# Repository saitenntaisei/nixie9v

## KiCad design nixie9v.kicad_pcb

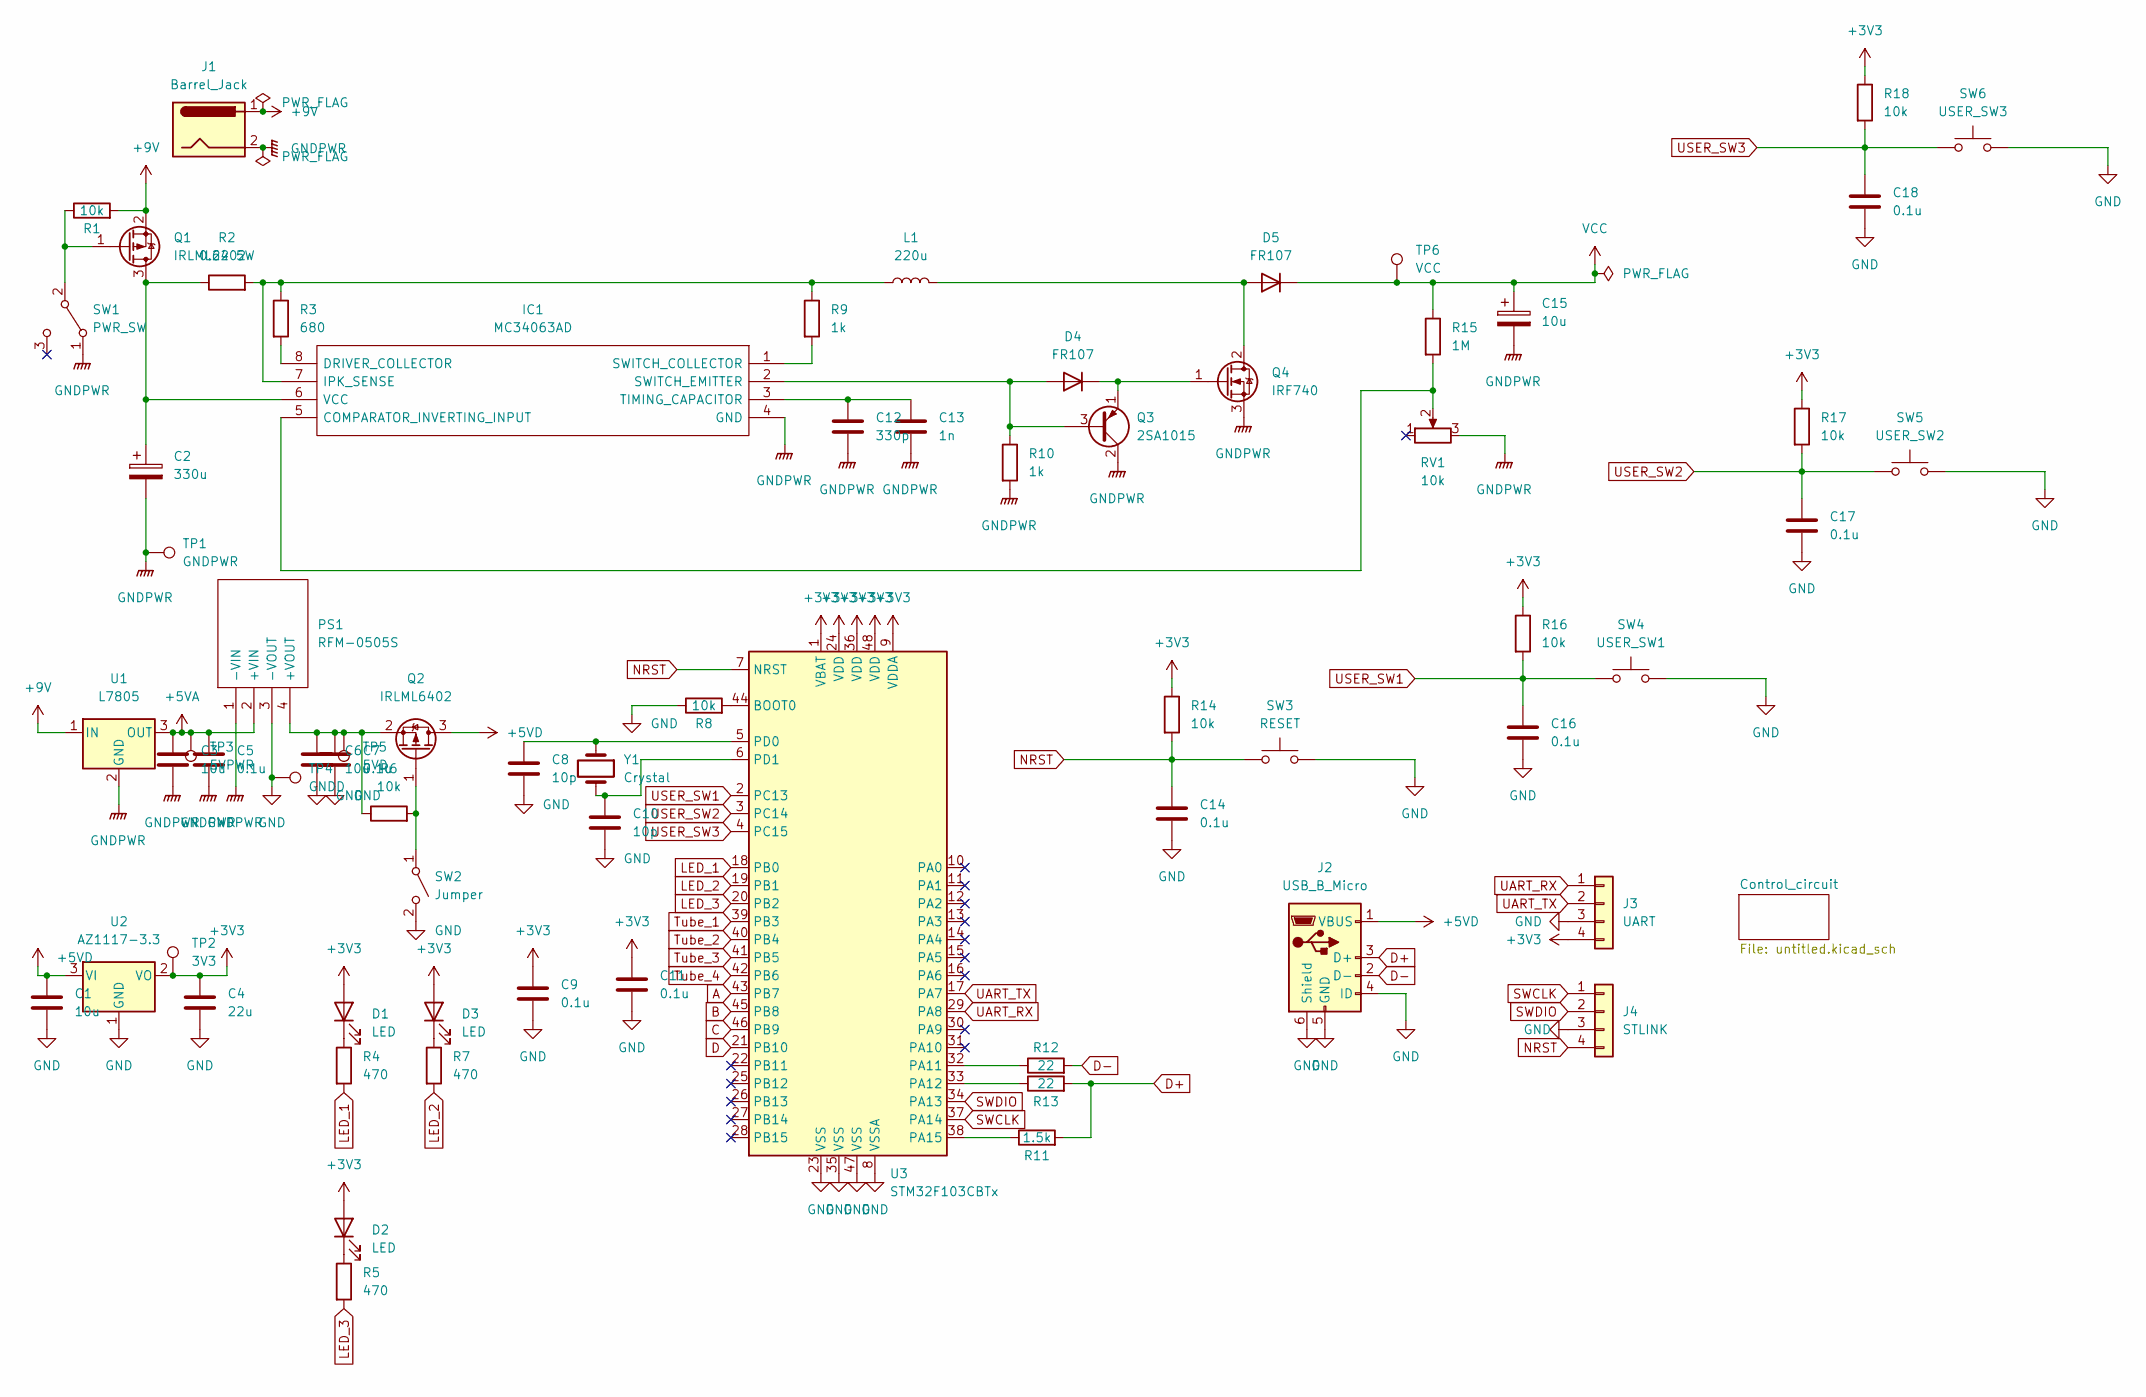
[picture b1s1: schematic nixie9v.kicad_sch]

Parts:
C1, C3, C6: 10u; C_0603_1608Metric_Pad1.08x0.95mm_HandSolder
C2: 330u; CP_Radial_D10.0mm_P3.50mm
C4: 22u; C_0603_1608Metric_Pad1.08x0.95mm_HandSolder
C5, C7, C9, C11, C14, C16, C17, C18: 0.1u; C_0603_1608Metric_Pad1.08x0.95mm_HandSolder
C8, C10: 10p; C_0603_1608Metric_Pad1.08x0.95mm_HandSolder
C12: 330p; C_0603_1608Metric_Pad1.08x0.95mm_HandSolder
C13: 1n; C_0603_1608Metric_Pad1.08x0.95mm_HandSolder
C15: 10u; CP_Radial_D10.0mm_P3.50mm
D1, D2, D3: LED; LED_0603_1608Metric_Pad1.05x0.95mm_HandSolder
D4, D5: FR107; D_DO-41_SOD81_P7.62mm_Horizontal
IC1: MC34063AD; SOIC127P600X175-8N; Manufacturer_Part_Number MC34063AD; Mouser Part Number 512-MC34063AD
J1: Barrel_Jack; BarrelJack_Horizontal
J2: USB_B_Micro; USB_Micro-B_Wuerth_629105150521_CircularHoles
J3: UART; JST_SH_BM04B-SRSS-TB_1x04-1MP_P1.00mm_Vertical
J4: STLINK; JST_SH_BM04B-SRSS-TB_1x04-1MP_P1.00mm_Vertical
L1: 220u; L_Toroid_Horizontal_D24.1mm_P21.80mm_Bourns_2200
PS1: RFM-0505S; RFM0505S; Manufacturer_Part_Number RFM-0505S; Mouser Part Number 919-RFM-0505S
Q1, Q2: IRLML6402; SOT-23
Q3: 2SA1015; TO-92
Q4: IRF740; TO-220-3_Vertical
R1, R6, R8, R14, R16, R17, R18: 10k; R_0603_1608Metric_Pad0.98x0.95mm_HandSolder
R2: 0.22 5W; RESM17073X710N
R3: 680; R_0603_1608Metric_Pad0.98x0.95mm_HandSolder
R4, R5, R7: 470; R_0603_1608Metric_Pad0.98x0.95mm_HandSolder
R9, R10: 1k; R_0603_1608Metric_Pad0.98x0.95mm_HandSolder
R11: 1.5k; R_0603_1608Metric_Pad0.98x0.95mm_HandSolder
R12, R13: 22; R_0603_1608Metric_Pad0.98x0.95mm_HandSolder
R15: 1M; R_0603_1608Metric_Pad0.98x0.95mm_HandSolder
RV1: 10k; 3362P_1
SW1: PWR_SW; PinHeader_1x03_P2.54mm_Vertical
SW2: Jumper; PinHeader_1x02_P2.54mm_Vertical
SW3: RESET; SW_SPST_EVQP2
SW4: USER_SW1; SW_SPST_EVQP2
SW5: USER_SW2; SW_SPST_EVQP2
SW6: USER_SW3; SW_SPST_EVQP2
TP1: GNDPWR; TestPoint_THTPad_D2.5mm_Drill1.2mm
TP2: 3V3; TestPoint_THTPad_D2.5mm_Drill1.2mm
TP3: 5VPWR; TestPoint_THTPad_D2.5mm_Drill1.2mm
TP4: GNDD; TestPoint_THTPad_D2.5mm_Drill1.2mm
TP5: 5VD; TestPoint_THTPad_D2.5mm_Drill1.2mm
TP6: VCC; TestPoint_THTPad_D2.5mm_Drill1.2mm
U1: L7805; TO-220-3_Vertical
U2: AZ1117-3.3; SOT-223-3_TabPin2
U3: STM32F103CBTx; LQFP-48_7x7mm_P0.5mm
Y1: Crystal; Crystal_SMD_SeikoEpson_MA505-2Pin_12.7x5.1mm_HandSoldering

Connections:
+3V3: C4.1, C9.1, C11.1, D1.2 (A), D2.2 (A), D3.2 (A), J3.4, R14.1, R16.1, R17.1, R18.1, TP2.1, U2.2 (VO), U3.1 (VBAT), U3.9 (VDDA), U3.24 (VDD), U3.36 (VDD), U3.48 (VDD); also elsewhere on the board
+5VA: C3.1, C5.1, PS1.2 (+VIN), TP3.1, U1.3 (OUT); also elsewhere on the board
+5VD: C1.1, J2.1 (VBUS), Q2.3 (D), U2.3 (VI)
+9V: J1.1, Q1.2 (S), R1.2, U1.1 (IN)
A: U3.43 (PB7); also elsewhere on the board
B: U3.45 (PB8); also elsewhere on the board
C: U3.46 (PB9); also elsewhere on the board
D: U3.21 (PB10); also elsewhere on the board
D+: J2.3 (D+), R11.2, R13.2
D-: J2.2 (D-), R12.2
GND: C1.2, C4.2, C6.2, C7.2, C8.2, C9.2, C10.2, C11.2, C14.2, C16.2, C17.2, C18.2, J2.4 (ID), J2.5 (GND), J2.6 (Shield), J3.3, J4.3, PS1.3 (-VOUT), R8.1, SW2.2 (B), SW3.2, SW4.2, SW5.2, SW6.2, TP4.1, U2.1 (GND), U3.8 (VSSA), U3.23 (VSS), U3.35 (VSS), U3.47 (VSS); also elsewhere on the board
LED_1: R4.2, U3.18 (PB0)
LED_2: R7.2, U3.19 (PB1)
LED_3: R5.2, U3.20 (PB2)
NRST: C14.1, J4.4, R14.2, SW3.1, U3.7 (NRST)
unnamed: C2.1, IC1.6 (VCC), Q1.3 (D), R2.1
unnamed: C6.1, C7.1, PS1.4 (+VOUT), Q2.2 (S), R6.1, TP5.1
unnamed: C8.1, U3.5 (PD0), Y1.1
unnamed: C10.1, U3.6 (PD1), Y1.2
unnamed: C12.1, C13.1, IC1.3 (TIMING_CAPACITOR)
unnamed: D1.1 (K), R4.1
unnamed: D2.1 (K), R5.1
unnamed: D3.1 (K), R7.1
unnamed: D4.1 (K), Q3.1 (E), Q4.1 (G)
unnamed: D4.2 (A), IC1.2 (SWITCH_EMITTER), Q3.3 (B), R10.1
unnamed: D5.2 (A), L1.2, Q4.2 (D)
unnamed: IC1.1 (SWITCH_COLLECTOR), R9.2
unnamed: IC1.5 (COMPARATOR_INVERTING_INPUT), R15.2, RV1.2
unnamed: IC1.7 (IPK_SENSE), L1.1, R2.2, R3.1, R9.1
unnamed: IC1.8 (DRIVER_COLLECTOR), R3.2
unnamed: Q1.1 (G), R1.1, SW1.2 (B)
unnamed: Q2.1 (G), R6.2, SW2.1 (A)
unnamed: R8.2, U3.44 (BOOT0)
unnamed: R11.1, U3.38 (PA15)
unnamed: R12.1, U3.32 (PA11)
unnamed: R13.1, U3.33 (PA12)
SWCLK: J4.1, U3.37 (PA14)
SWDIO: J4.2, U3.34 (PA13)
Tube_1: U3.39 (PB3); also elsewhere on the board
Tube_2: U3.40 (PB4); also elsewhere on the board
Tube_3: U3.41 (PB5); also elsewhere on the board
Tube_4: U3.42 (PB6); also elsewhere on the board
UART_RX: J3.1, U3.29 (PA8)
UART_TX: J3.2, U3.17 (PA7)
USER_SW1: C16.1, R16.2, SW4.1, U3.2 (PC13)
USER_SW2: C17.1, R17.2, SW5.1, U3.3 (PC14)
USER_SW3: C18.1, R18.2, SW6.1, U3.4 (PC15)
VCC: C15.1, D5.1 (K), R15.1, TP6.1; also elsewhere on the board

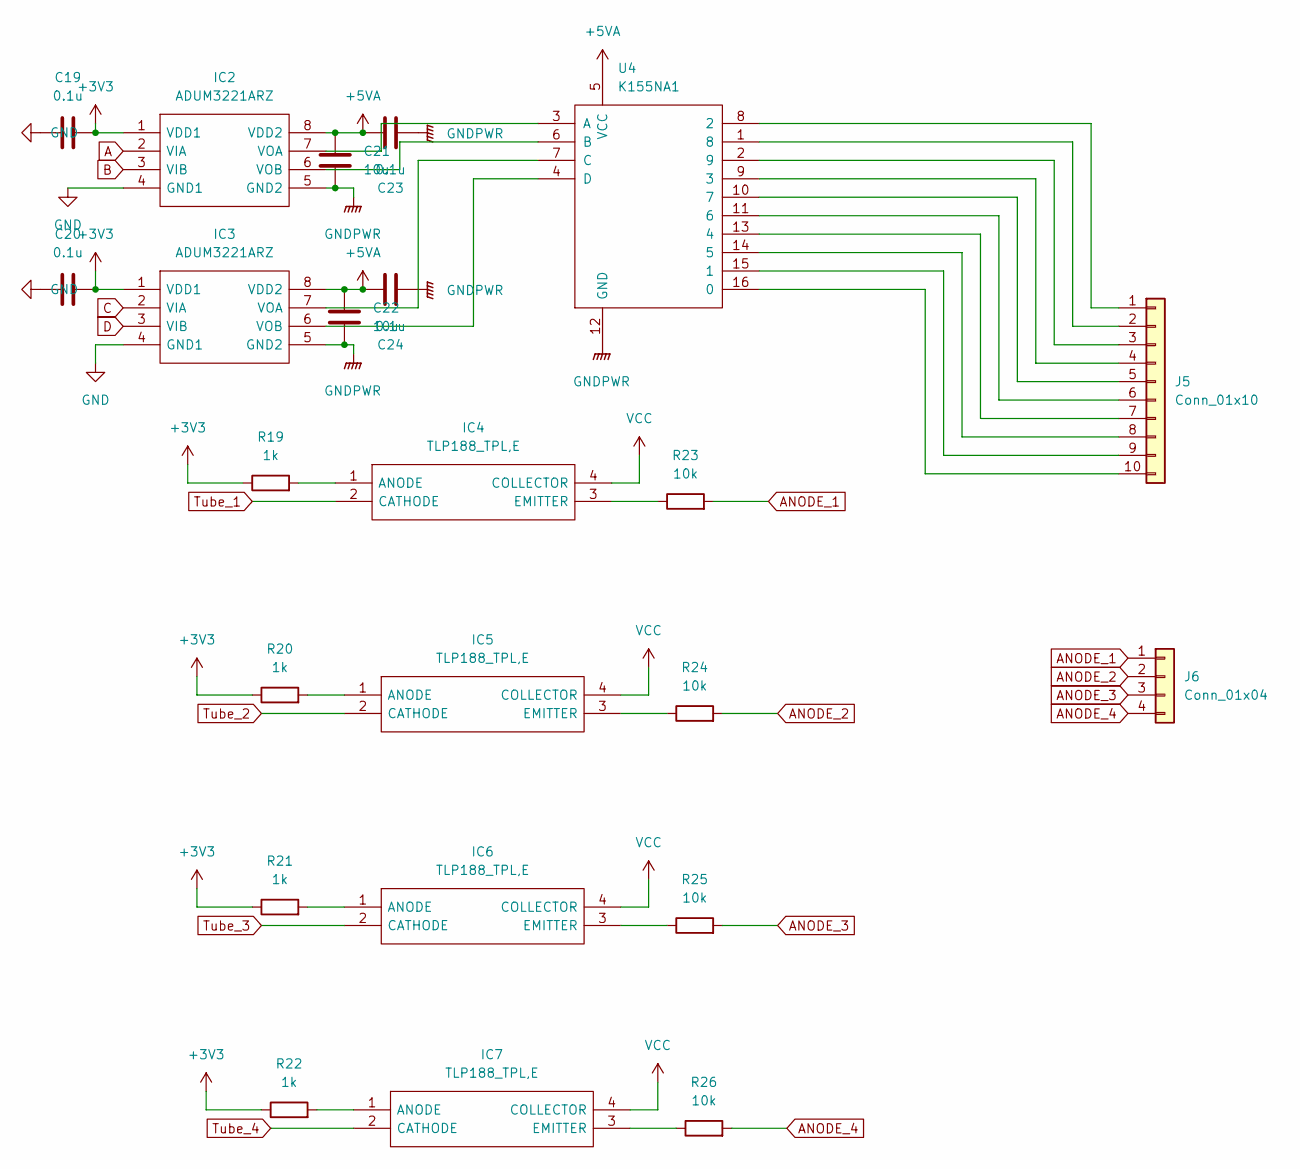
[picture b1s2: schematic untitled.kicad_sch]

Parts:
C19, C20, C23, C24: 0.1u; C_0603_1608Metric_Pad1.08x0.95mm_HandSolder
C21, C22: 10u; C_0603_1608Metric_Pad1.08x0.95mm_HandSolder
IC2, IC3: ADUM3221ARZ; SOIC127P600X175-8N; Manufacturer_Part_Number ADUM3221ARZ; Mouser Part Number 584-ADUM3221ARZ
IC4, IC5, IC6, IC7: TLP188_TPL,E; SOP254P700X220-4N; Manufacturer_Part_Number TLP188(TPL,E; Mouser Part Number 757-TLP188(TPLE
J5: Conn_01x10; PinSocket_1x10_P2.54mm_Vertical
J6: Conn_01x04; PinSocket_1x04_P2.54mm_Vertical
R19, R20, R21, R22: 1k; R_0603_1608Metric_Pad0.98x0.95mm_HandSolder
R23, R24, R25, R26: 10k; R_0603_1608Metric_Pad0.98x0.95mm_HandSolder
U4: K155NA1; DIP787W53P279L2176H508Q16N

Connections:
+3V3: C19.2, C20.2, IC2.1 (VDD1), IC3.1 (VDD1), R19.1, R20.1, R21.1, R22.1; also elsewhere on the board
+5VA: C21.2, C22.2, C23.2, C24.2, IC2.8 (VDD2), IC3.8 (VDD2), U4.5 (VCC); also elsewhere on the board
A: IC2.2 (VIA); also elsewhere on the board
ANODE_1: J6.1, R23.2
ANODE_2: J6.2, R24.2
ANODE_3: J6.3, R25.2
ANODE_4: J6.4, R26.2
B: IC2.3 (VIB); also elsewhere on the board
C: IC3.2 (VIA); also elsewhere on the board
D: IC3.3 (VIB); also elsewhere on the board
GND: C19.1, C20.1, IC2.4 (GND1), IC3.4 (GND1); also elsewhere on the board
unnamed: IC2.6 (VOB), U4.6 (B)
unnamed: IC2.7 (VOA), U4.3 (A)
unnamed: IC3.6 (VOB), U4.4 (D)
unnamed: IC4.1 (ANODE), R19.2
unnamed: IC4.3 (EMITTER), R23.1
unnamed: IC5.1 (ANODE), R20.2
unnamed: IC5.3 (EMITTER), R24.1
unnamed: IC6.1 (ANODE), R21.2
unnamed: IC7.1 (ANODE), R22.2
unnamed: IC7.3 (EMITTER), R26.1
unnamed: J5.1, U4.8 (2)
unnamed: J5.2, U4.1 (8)
unnamed: J5.3, U4.2 (9)
unnamed: J5.4, U4.9 (3)
unnamed: J5.5, U4.10 (7)
unnamed: J5.6, U4.11 (6)
unnamed: J5.7, U4.13 (4)
unnamed: J5.8, U4.14 (5)
unnamed: J5.9, U4.15 (1)
unnamed: J5.10, U4.16 (0)
unnamed: IC6.3 (EMITTER), R25.1
Tube_1: IC4.2 (CATHODE); also elsewhere on the board
Tube_2: IC5.2 (CATHODE); also elsewhere on the board
Tube_3: IC6.2 (CATHODE); also elsewhere on the board
Tube_4: IC7.2 (CATHODE); also elsewhere on the board
VCC: IC4.4 (COLLECTOR), IC5.4 (COLLECTOR), IC6.4 (COLLECTOR), IC7.4 (COLLECTOR); also elsewhere on the board

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
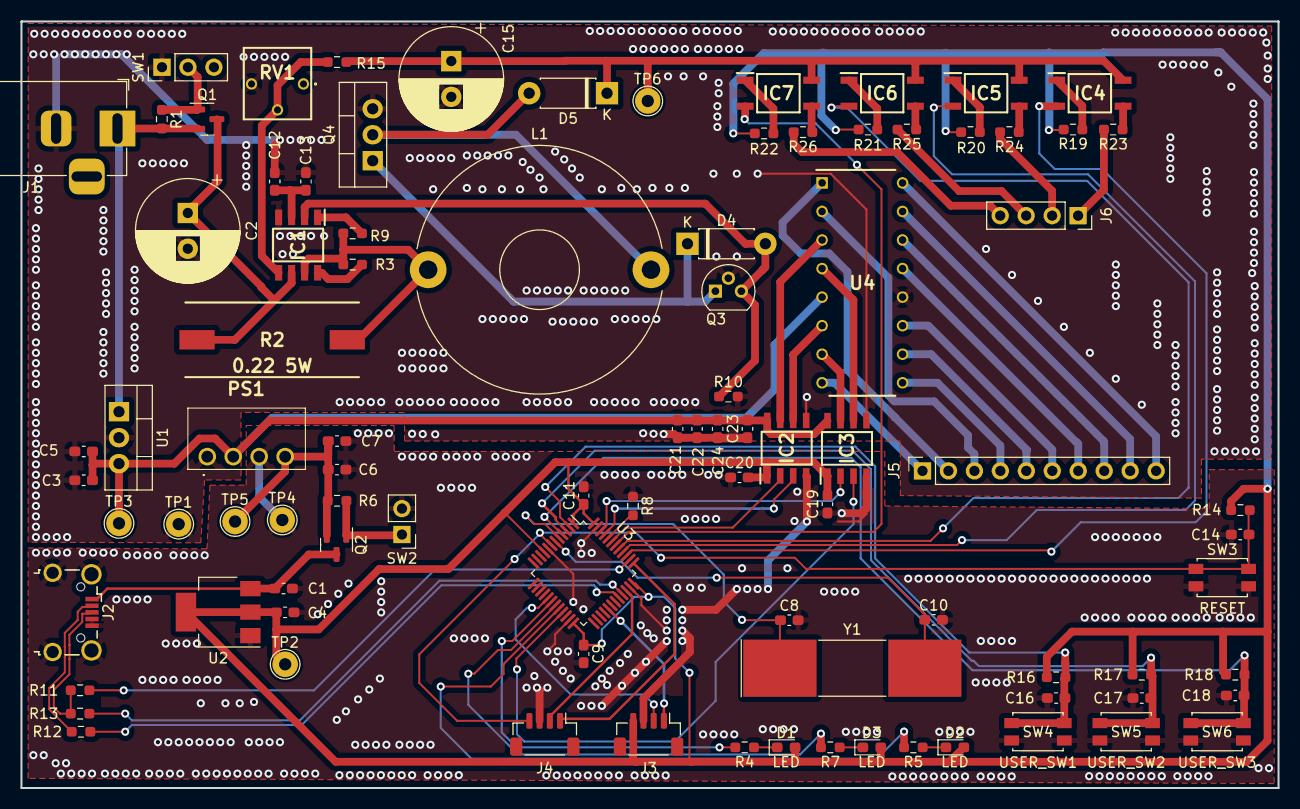
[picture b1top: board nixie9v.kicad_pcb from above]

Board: 2 copper layers, 123.0 x 75.0 mm, 92 parts (0 on the bottom side), 75 nets.

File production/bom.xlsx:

Designator | Footprint | Quantity | Value | LCSC Part # | LCSC Part #
C1, C21, C22, C3, C6 | C_0603_1608Metric_Pad1.08x0.95mm_HandSolder | 5 | 10u
C10, C8 | C_0603_1608Metric_Pad1.08x0.95mm_HandSolder | 2 | 10p |  |  | 11
C11, C14, C16, C17, C18, C19, C20, C23, C24, C5, C7, C9 | C_0603_1608Metric_Pad1.08x0.95mm_HandSolder | 12 | 0.1u
C12 | C_0603_1608Metric_Pad1.08x0.95mm_HandSolder | 1 | 330p |  |  | 12
C13 | C_0603_1608Metric_Pad1.08x0.95mm_HandSolder | 1 | 1n
C15 | CP_Radial_D10.0mm_P3.50mm | 1 | 10u |  |  | 13
C2 | CP_Radial_D10.0mm_P3.50mm | 1 | 330u |  |  | 14
C4 | C_0603_1608Metric_Pad1.08x0.95mm_HandSolder | 1 | 22u
D1, D2, D3 | LED_0603_1608Metric_Pad1.05x0.95mm_HandSolder | 3 | LED
D4, D5 | D_DO-41_SOD81_P7.62mm_Horizontal | 2 | FR107
IC1 | SOIC127P600X175-8N | 1 | MC34063AD
IC2, IC3 | SOIC127P600X175-8N | 2 | ADUM3221ARZ |  |  | 1
IC4, IC5, IC6, IC7 | SOP254P700X220-4N | 4 | TLP188_TPL,E |  |  | 2
J1 | BarrelJack_Horizontal | 1 | Barrel_Jack
J2 | USB_Micro-B_Wuerth_629105150521_CircularHoles | 1 | USB_B_Micro |  |  | 3
J3 | JST_SH_BM04B-SRSS-TB_1x04-1MP_P1.00mm_Vertical | 1 | UART
J4 | JST_SH_BM04B-SRSS-TB_1x04-1MP_P1.00mm_Vertical | 1 | STLINK
J5 | PinSocket_1x10_P2.54mm_Vertical | 1 | Conn_01x10
J6 | PinSocket_1x04_P2.54mm_Vertical | 1 | Conn_01x04
L1 | L_Toroid_Horizontal_D24.1mm_P21.80mm_Bourns_2200 | 1 | 220u |  |  | 4
PS1 | RFM0505S | 1 | RFM-0505S
Q1, Q2 | SOT-23 | 2 | IRLML6402
Q3 | TO-92 | 1 | 2SA1015
Q4 | TO-220-3_Vertical | 1 | IRF740
R1, R14, R16, R17, R18, R23, R24, R25, R26, R6, R8 | R_0603_1608Metric_Pad0.98x0.95mm_HandSolder | 11 | 10k |  |  | 5
R10, R19, R20, R21, R22, R9 | R_0603_1608Metric_Pad0.98x0.95mm_HandSolder | 6 | 1k
R11 | R_0603_1608Metric_Pad0.98x0.95mm_HandSolder | 1 | 1.5k |  |  | 6
R12, R13 | R_0603_1608Metric_Pad0.98x0.95mm_HandSolder | 2 | 22 |  |  | 7
R15 | R_0603_1608Metric_Pad0.98x0.95mm_HandSolder | 1 | 1M |  |  | 8
R2 | RESM17073X710N | 1 | 0.22 5W |  |  | 9
R3 | R_0603_1608Metric_Pad0.98x0.95mm_HandSolder | 1 | 680
R4, R5, R7 | R_0603_1608Metric_Pad0.98x0.95mm_HandSolder | 3 | 470 |  |  | 10
RV1 | 3362P_1 | 1 | 10k
SW1 | PinHeader_1x03_P2.54mm_Vertical | 1 | PWR_SW
SW2 | PinHeader_1x02_P2.54mm_Vertical | 1 | Jumper
SW3 | SW_SPST_EVQP2 | 1 | RESET
SW4 | SW_SPST_EVQP2 | 1 | USER_SW1
SW5 | SW_SPST_EVQP2 | 1 | USER_SW2
SW6 | SW_SPST_EVQP2 | 1 | USER_SW3
TP1 | TestPoint_THTPad_D2.5mm_Drill1.2mm | 1 | GNDPWR
TP2 | TestPoint_THTPad_D2.5mm_Drill1.2mm | 1 | 3V3
TP3 | TestPoint_THTPad_D2.5mm_Drill1.2mm | 1 | 5VPWR
TP4 | TestPoint_THTPad_D2.5mm_Drill1.2mm | 1 | GNDD
TP5 | TestPoint_THTPad_D2.5mm_Drill1.2mm | 1 | 5VD
TP6 | TestPoint_THTPad_D2.5mm_Drill1.2mm | 1 | VCC
U1 | TO-220-3_Vertical | 1 | L7805
U2 | SOT-223-3_TabPin2 | 1 | AZ1117-3.3
U3 | LQFP-48_7x7mm_P0.5mm | 1 | STM32F103CBTx
U4 | DIP787W53P279L2176H508Q16N | 1 | K155NA1
Y1 | Crystal_SMD_SeikoEpson_MA505-2Pin_12.7x5.1mm_HandSoldering | 1 | Crystal

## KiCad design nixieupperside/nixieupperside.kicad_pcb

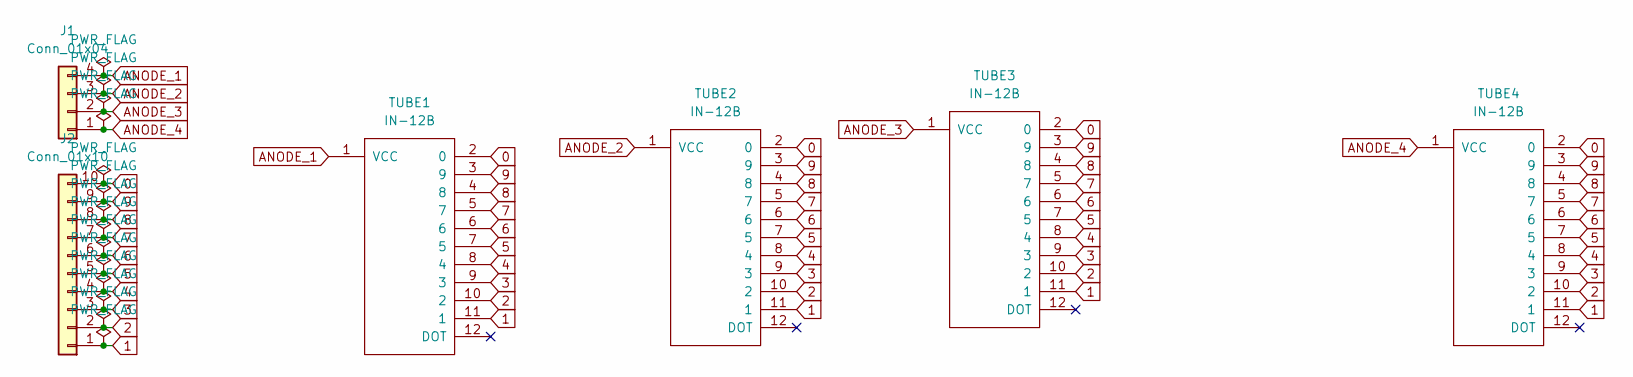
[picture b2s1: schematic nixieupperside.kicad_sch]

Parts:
J1: Conn_01x04; PinHeader_1x04_P2.54mm_Vertical
J2: Conn_01x10; PinHeader_1x10_P2.54mm_Vertical
TUBE1, TUBE2, TUBE3, TUBE4: IN-12B

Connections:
0: J2.10, TUBE1.2 (0), TUBE2.2 (0), TUBE3.2 (0), TUBE4.2 (0)
1: J2.1, TUBE1.11 (1), TUBE2.11 (1), TUBE3.11 (1), TUBE4.11 (1)
2: J2.2, TUBE1.10 (2), TUBE2.10 (2), TUBE3.10 (2), TUBE4.10 (2)
3: J2.3, TUBE1.9 (3), TUBE2.9 (3), TUBE3.9 (3), TUBE4.9 (3)
4: J2.4, TUBE1.8 (4), TUBE2.8 (4), TUBE3.8 (4), TUBE4.8 (4)
5: J2.5, TUBE1.7 (5), TUBE2.7 (5), TUBE3.7 (5), TUBE4.7 (5)
6: J2.6, TUBE1.6, TUBE2.6, TUBE3.6, TUBE4.6
7: J2.7, TUBE1.5 (7), TUBE2.5 (7), TUBE3.5 (7), TUBE4.5 (7)
8: J2.8, TUBE1.4 (8), TUBE2.4 (8), TUBE3.4 (8), TUBE4.4 (8)
9: J2.9, TUBE1.3 (9), TUBE2.3 (9), TUBE3.3 (9), TUBE4.3 (9)
ANODE_1: J1.4, TUBE1.1 (VCC)
ANODE_2: J1.3, TUBE2.1 (VCC)
ANODE_3: J1.2, TUBE3.1 (VCC)
ANODE_4: J1.1, TUBE4.1 (VCC)

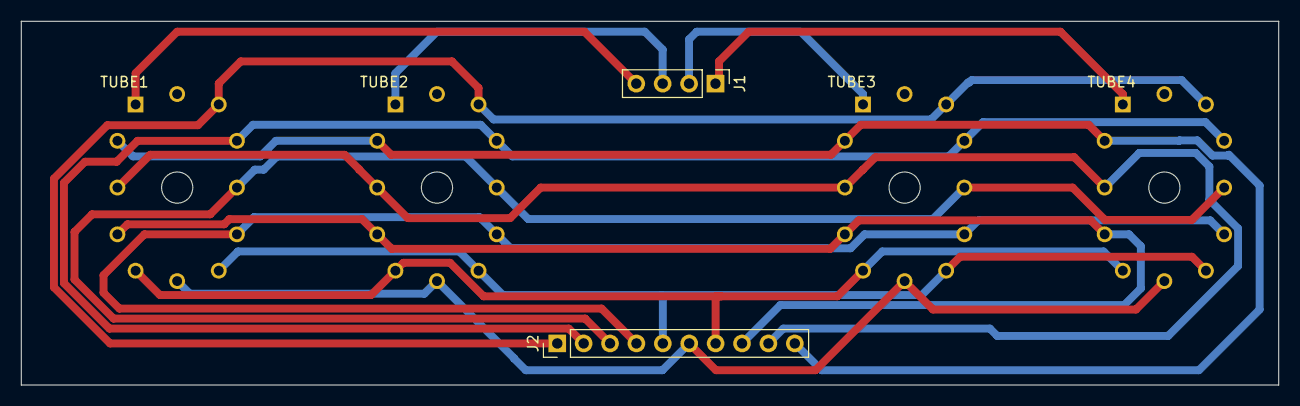
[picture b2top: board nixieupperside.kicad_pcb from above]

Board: 2 copper layers, 121.0 x 35.0 mm, 6 parts (0 on the bottom side), 14 nets.

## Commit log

2022-12-12 add mcu
2022-12-12 sch accomplished
2022-12-13 add switch and footprint mapping in the middle
2022-12-13 schema finished
2022-12-15 upperside
2022-12-15 accomplished
2022-12-27 fix Q3 orietention
2022-12-29 production
2022-12-30 fix direction tlp188
